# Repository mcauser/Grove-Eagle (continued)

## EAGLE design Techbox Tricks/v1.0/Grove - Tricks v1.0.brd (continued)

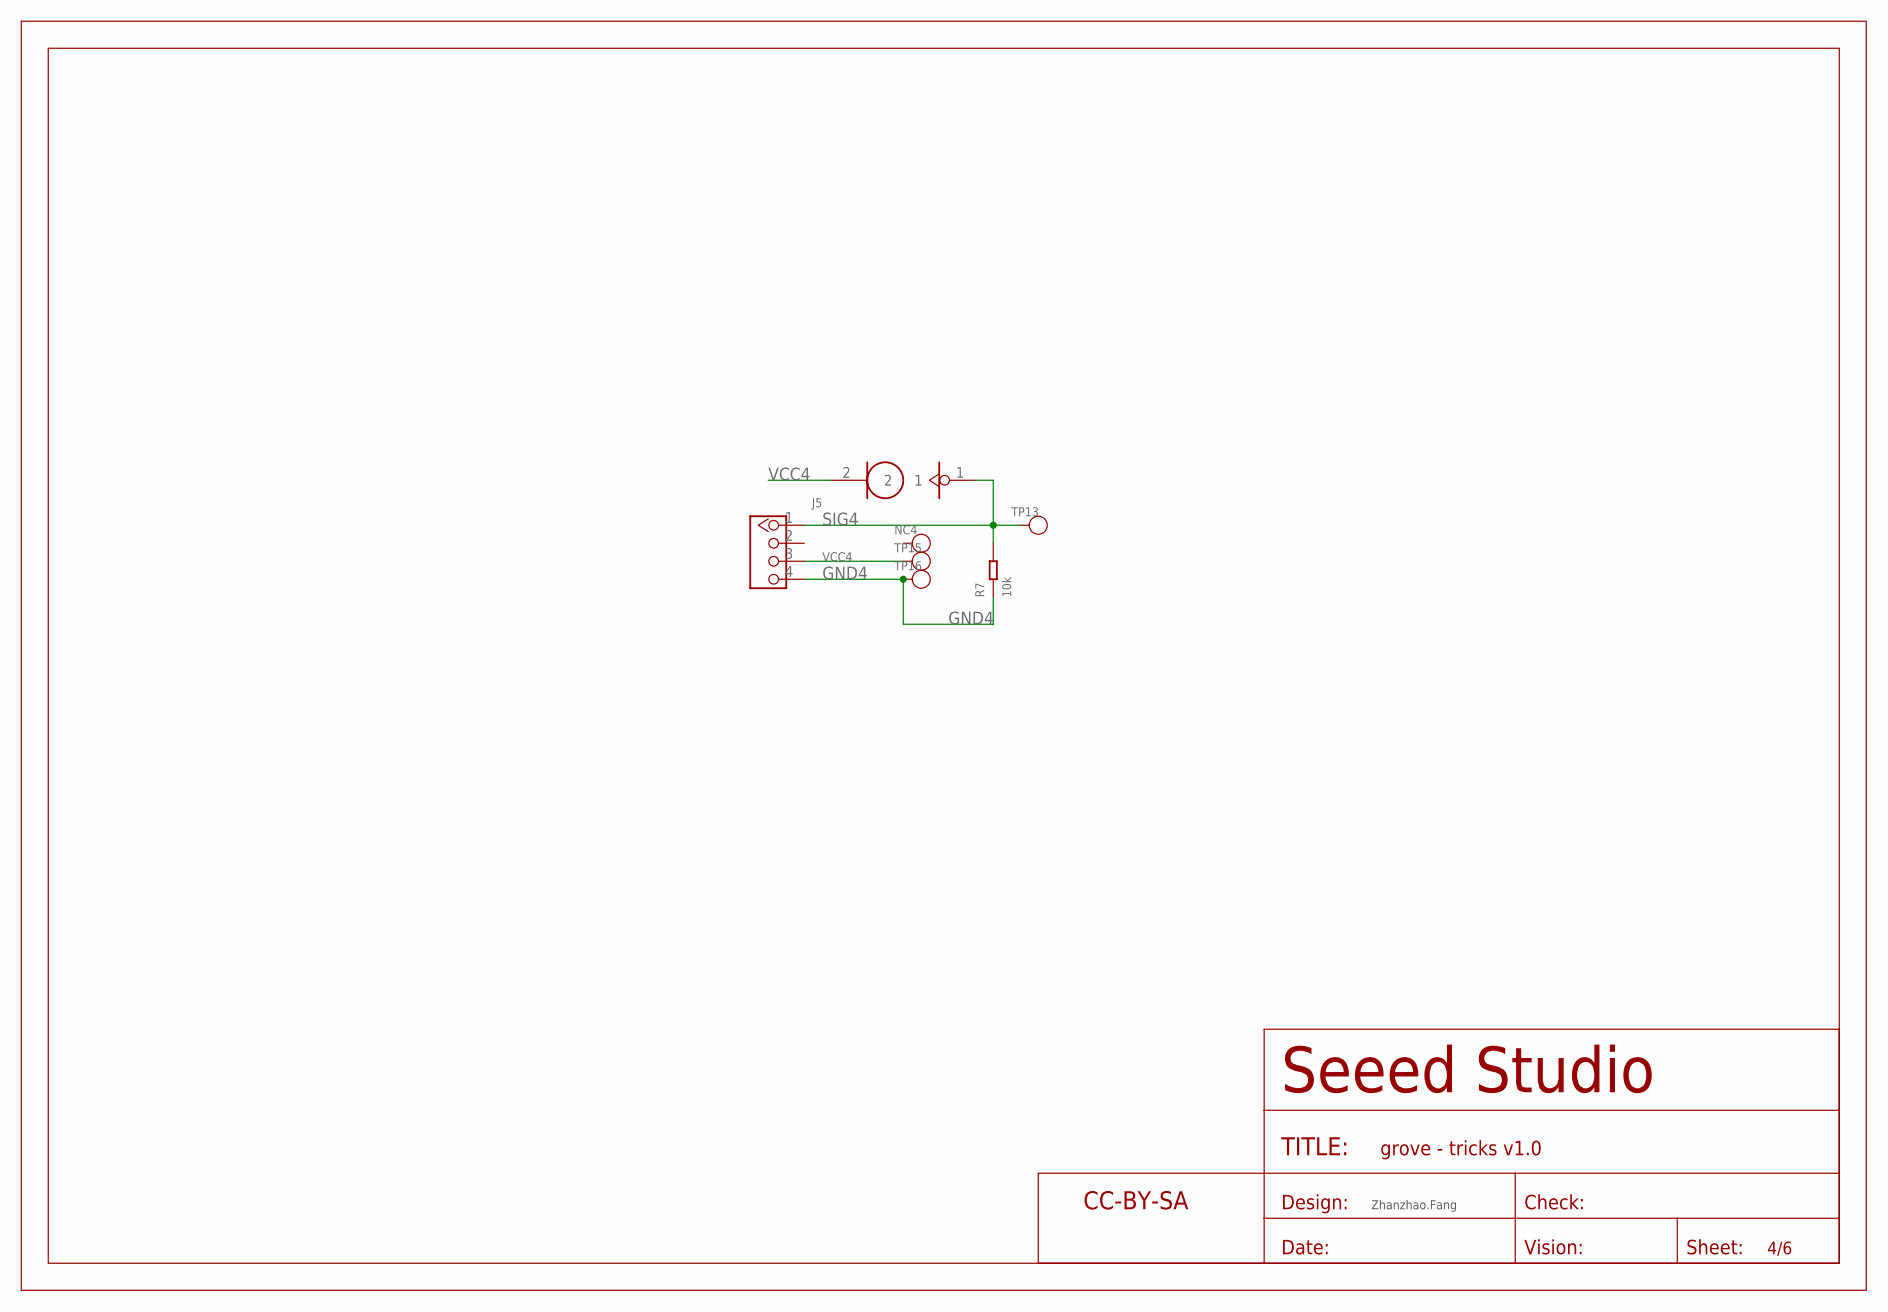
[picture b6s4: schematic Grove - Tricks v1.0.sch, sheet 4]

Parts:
J4: TILT
J5: GROVE-CONNECTOR-DIP-2.0; HW4-2.0
NC4: TEST-POINT'4545'; TP-D45MIL
R7: 10k; R0603
TP13, TP15, TP16: TEST-POINT'4545'; TP-D45MIL
U$5: SEEEDSTUDIO-OPEN-SCH-FRAME; SEEEDSTUDIO-PCB-FRAME

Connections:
GND4: J5.4, R7.1, TP16.T
SIG4: J4.1, J5.1, R7.2, TP13.T
VCC4: J4.2, J5.3, TP15.T

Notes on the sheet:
Zhanzhao.Fang

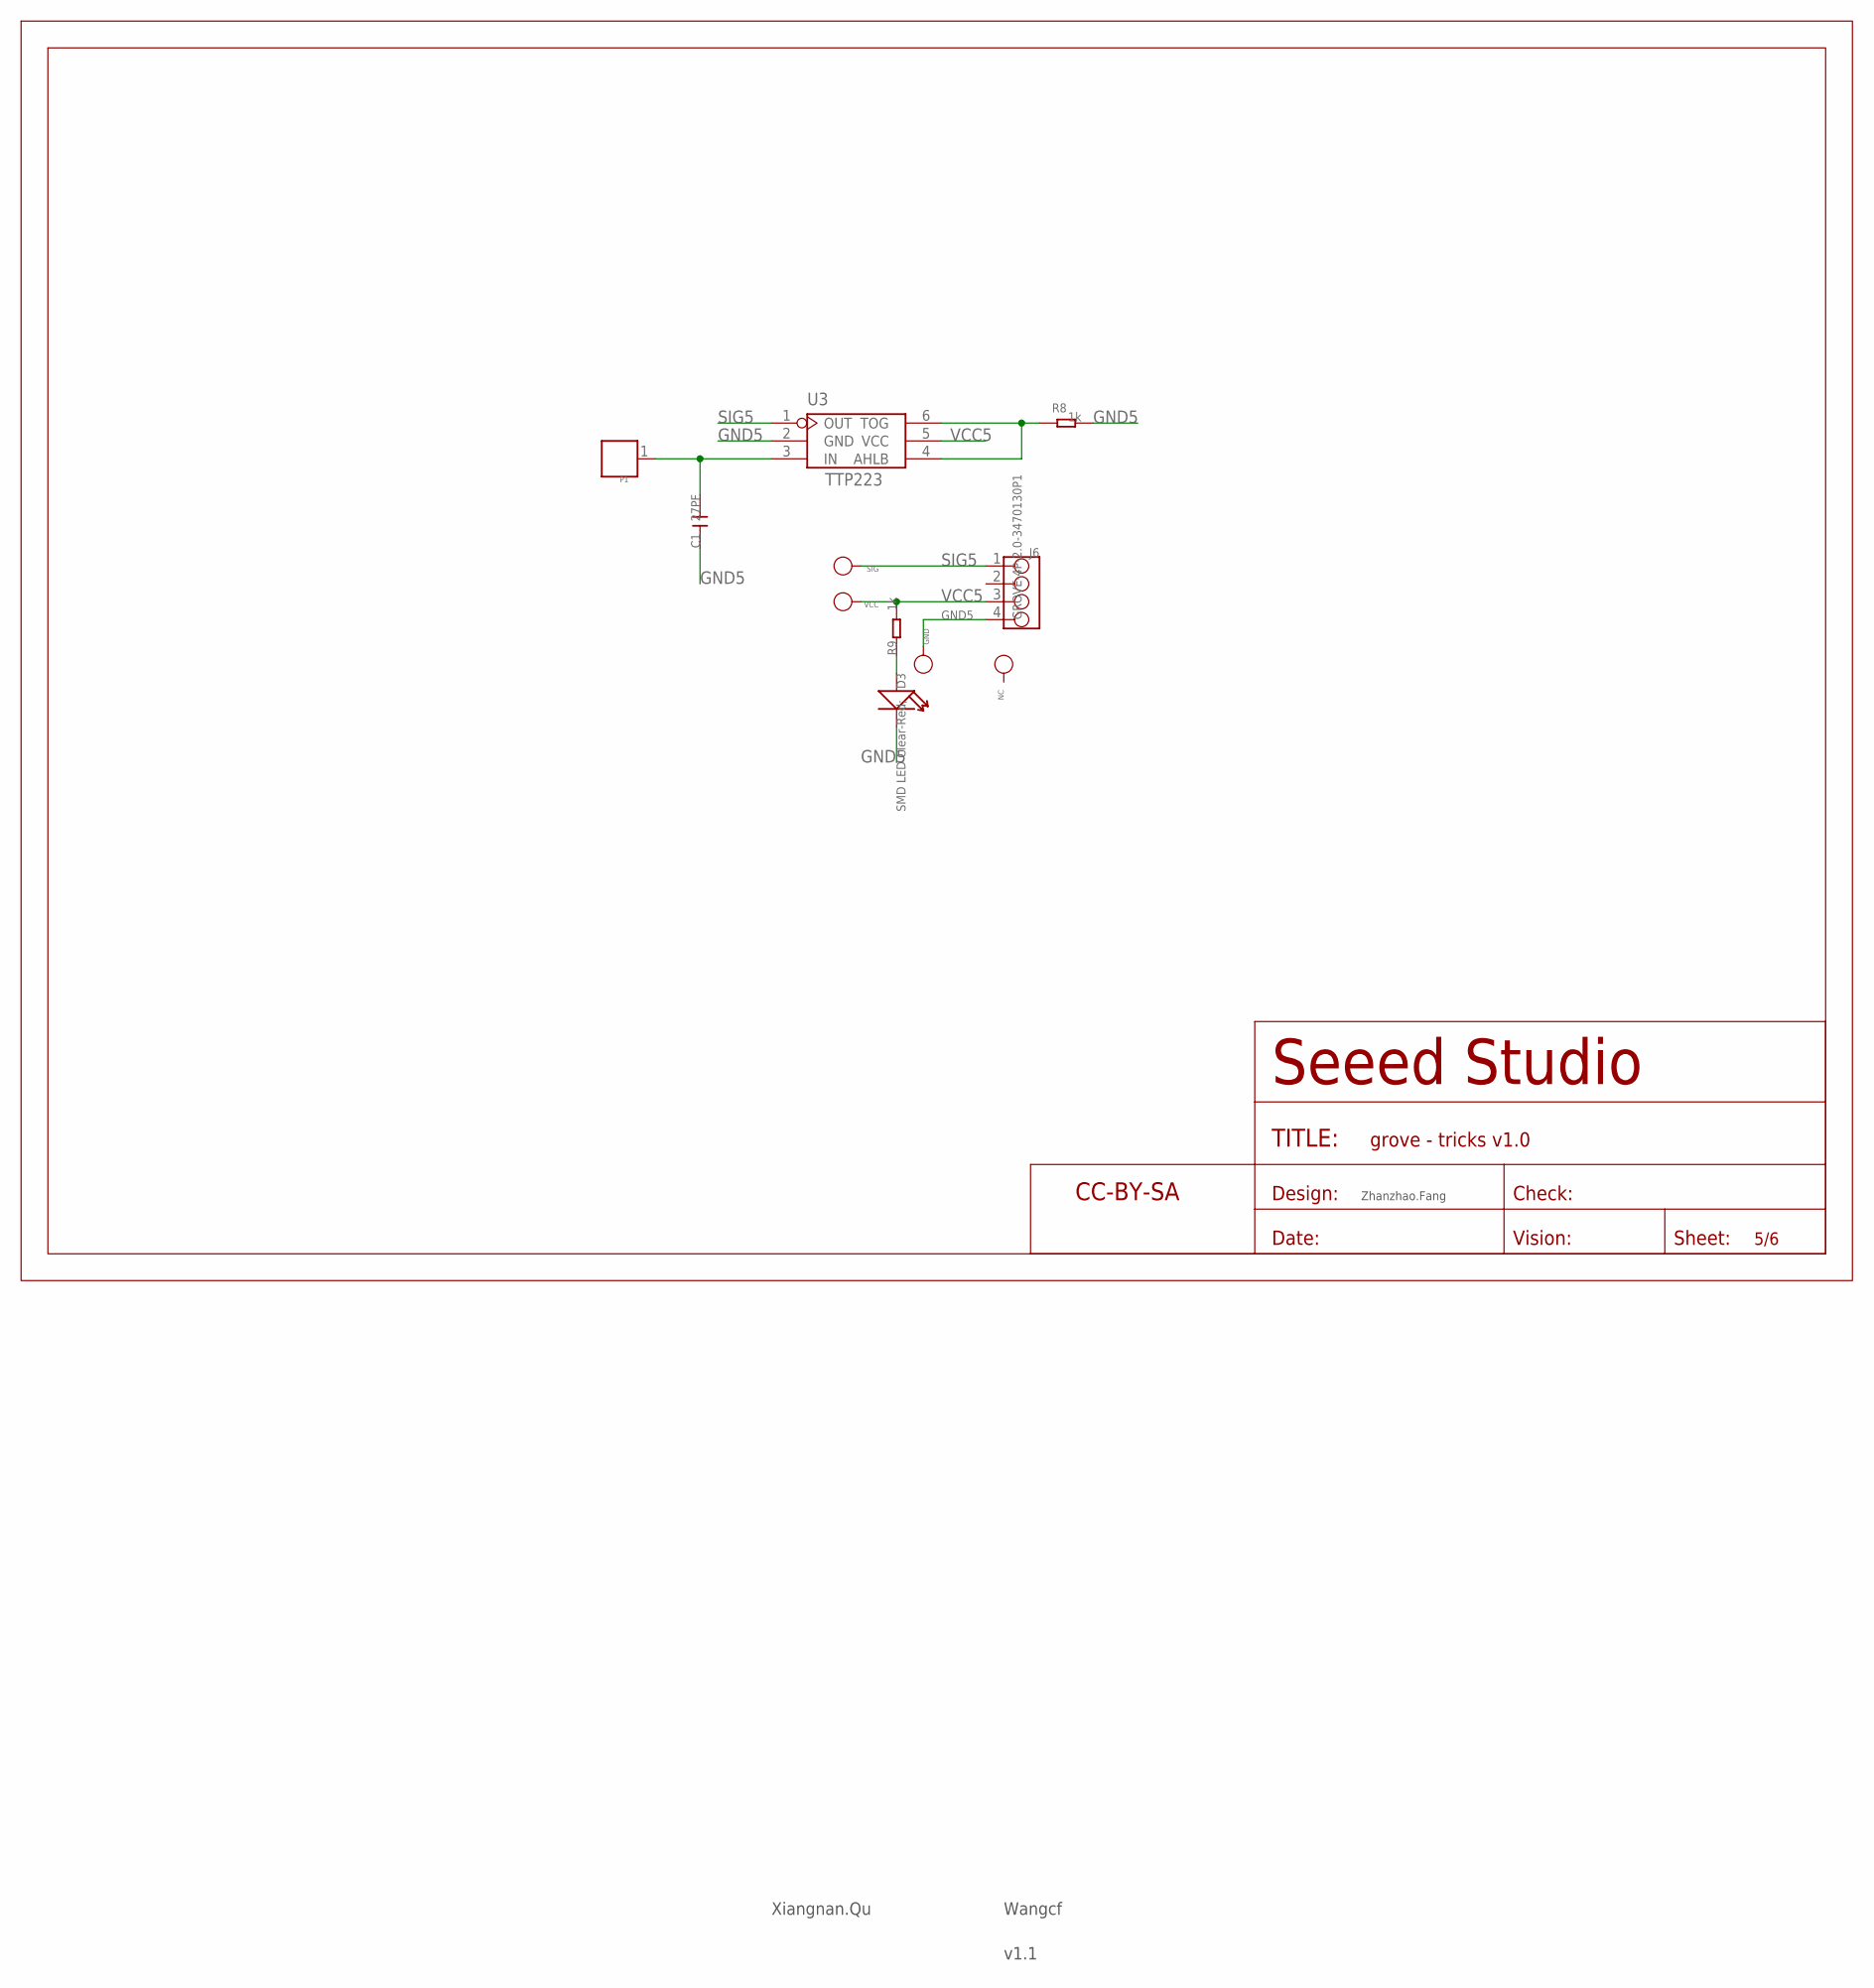
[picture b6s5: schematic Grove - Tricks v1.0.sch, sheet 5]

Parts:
C1: 27PF; C0603
D3: SMD LED Clear-Red;; LED-0603
GND: PAD-TEST-POINT'4545'; TP_4545
J6: GROVE-4P-2.0-3470130P1; 4P-2.0
NC: PAD-TEST-POINT'4545'; TP_4545
P1: PAD'D450MIL'; 1P-D450
R8, R9: 1k; R0603
SIG: PAD-TEST-POINT'4545'; TP_4545
U3: TTP223; SOT23-6L
U$12: SEEEDSTUDIO-OPEN-SCH-FRAME; SEEEDSTUDIO-PCB-FRAME
VCC: PAD-TEST-POINT'4545'; TP_4545

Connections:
GND5: C1.1, D3.-, GND.T, J6.4, R8.2, U3.2 (GND)
IN: C1.2, P1.1, U3.3 (IN)
unnamed: R8.1, U3.4 (AHLB), U3.6 (TOG)
unnamed: D3.+, R9.1
SIG5: J6.1, SIG.T, U3.1 (OUT)
VCC5: J6.3, R9.2, U3.5 (VCC), VCC.T

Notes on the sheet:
TTP223
Xiangnan.Qu
Wangcf
v1.1
Zhanzhao.Fang

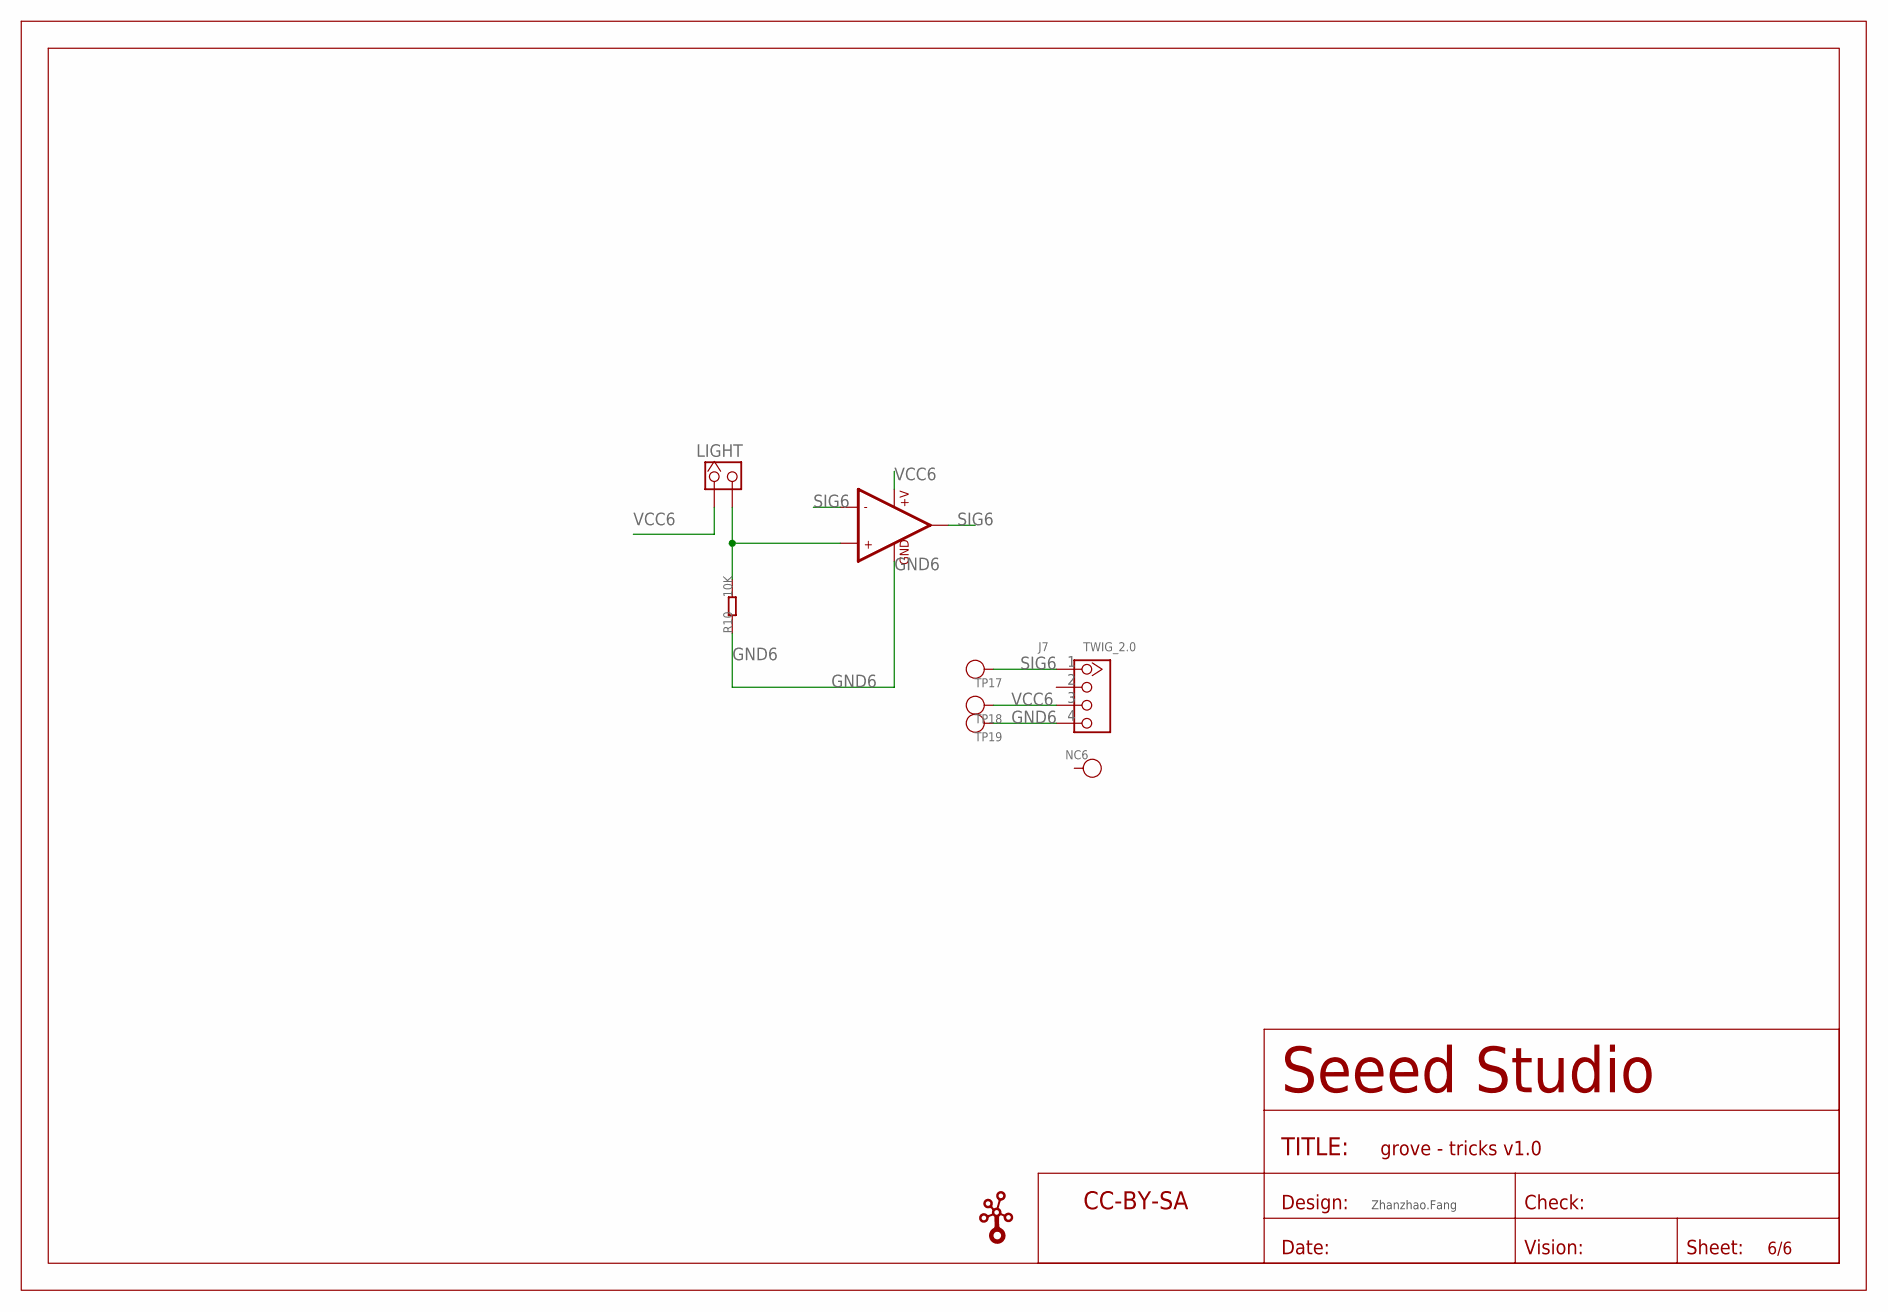
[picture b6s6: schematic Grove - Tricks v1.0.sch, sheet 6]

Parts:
J7: TWIG_2.0; HW4-2.0
LIGHT: HEADER_1X2_2.54; CK_1*2
NC6: TEST-POINT'4545'; TP-D45MIL
R10: 10K; 0603
TP17, TP18, TP19: TEST-POINT'4545'; TP-D45MIL
U4: LMV358; SO08
U$13: SEEEDSTUDIO-OPEN-SCH-FRAME; SEEEDSTUDIO-PCB-FRAME
U$16: TWIGLOGOTWIGLOGO_SMALL; TWIGLOGO_SMALL

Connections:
GND6: J7.4, R10.1, TP19.T, U4.4 (GND)
unnamed: LIGHT.2, R10.2, U4.3 (+IN1)
SIG6: J7.1, TP17.T, U4.1 (OUT1), U4.2 (-IN1)
VCC6: J7.3, LIGHT.1, TP18.T, U4.8 (+V)

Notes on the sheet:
Zhanzhao.Fang

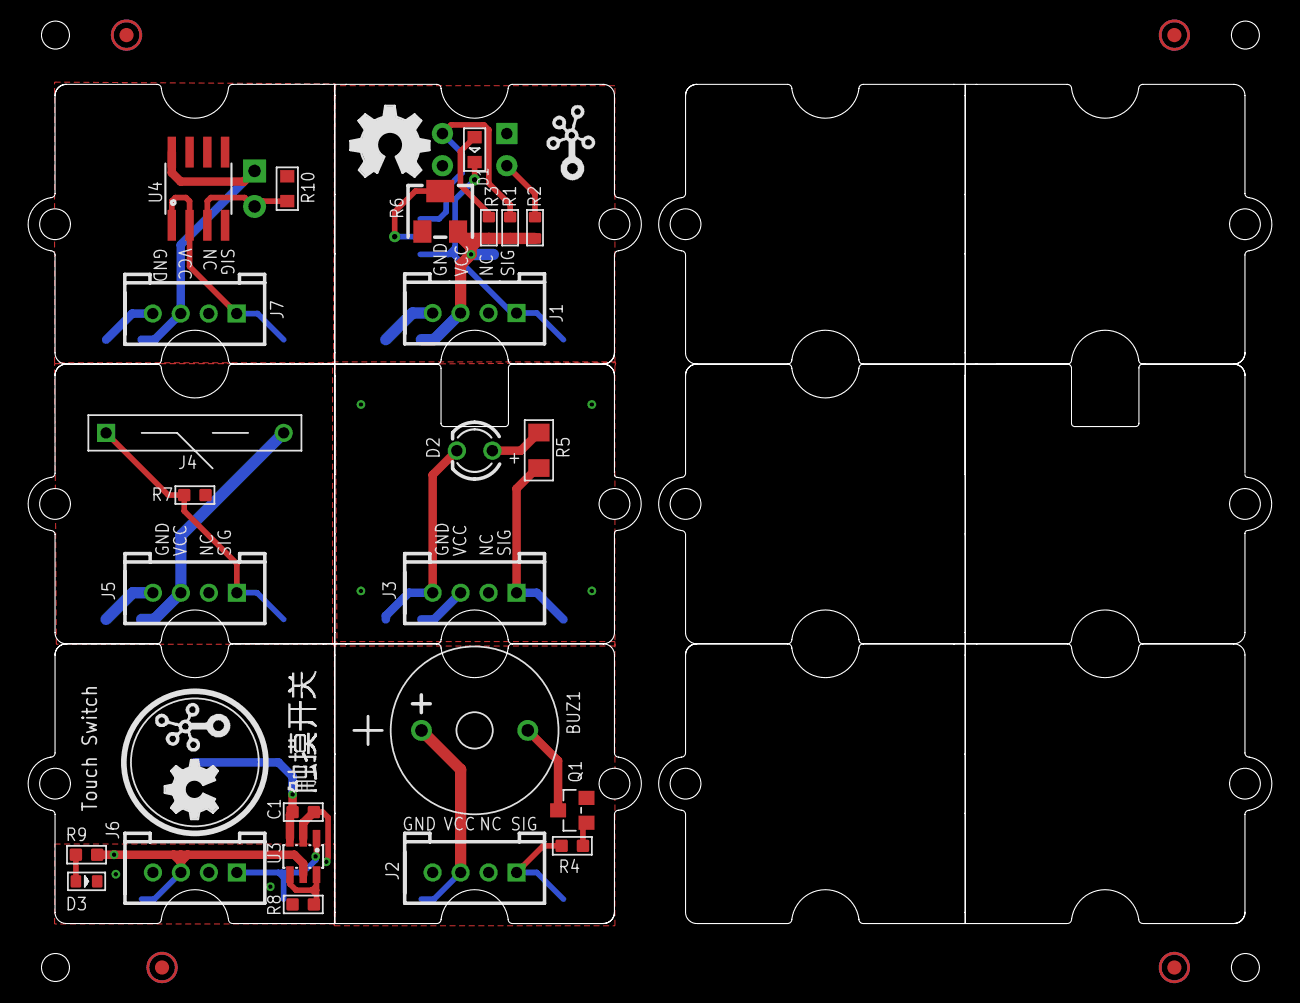
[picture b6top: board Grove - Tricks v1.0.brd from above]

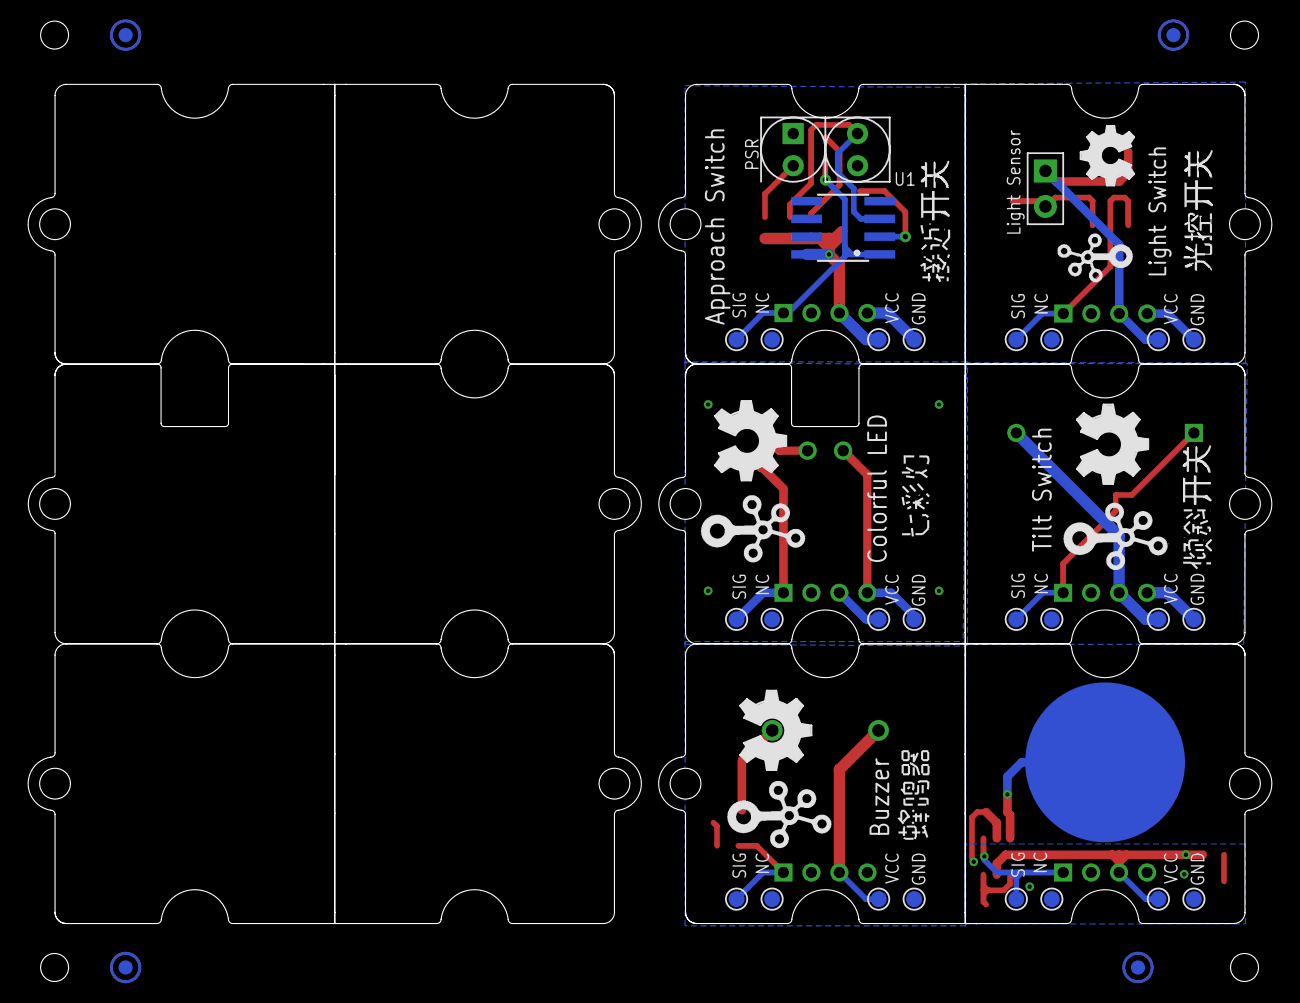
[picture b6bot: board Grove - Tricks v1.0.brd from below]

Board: 2 copper layers, 88.9 x 60.0 mm, 91 parts (40 on the bottom side), 29 nets.

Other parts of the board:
TWIG1, TWIG2, TWIG3, TWIG4, TWIG5, TWIG6, TWIG7, TWIG8, TWIG9, TWIG10: GROVE-1*1-TEST-PLATFORM@1
U2: GROVE-1*1-TEST-PLATFORM-LED
U$1, U$7, U$10, U$11: OSHW_FILLX200_NOTEXT
U$8, U$9, U$18: TWIGLOGO
U$14, U$17: OSHW_FILLX150_NOTEXT
U$15: TWIGLOGO_SMALL
